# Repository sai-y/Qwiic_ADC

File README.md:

# Qwiic_ADC

Repo for an ADC chip that uses the Qwiic connector interface from Sparkfun

The ADC chip used here is the ADS7828EB

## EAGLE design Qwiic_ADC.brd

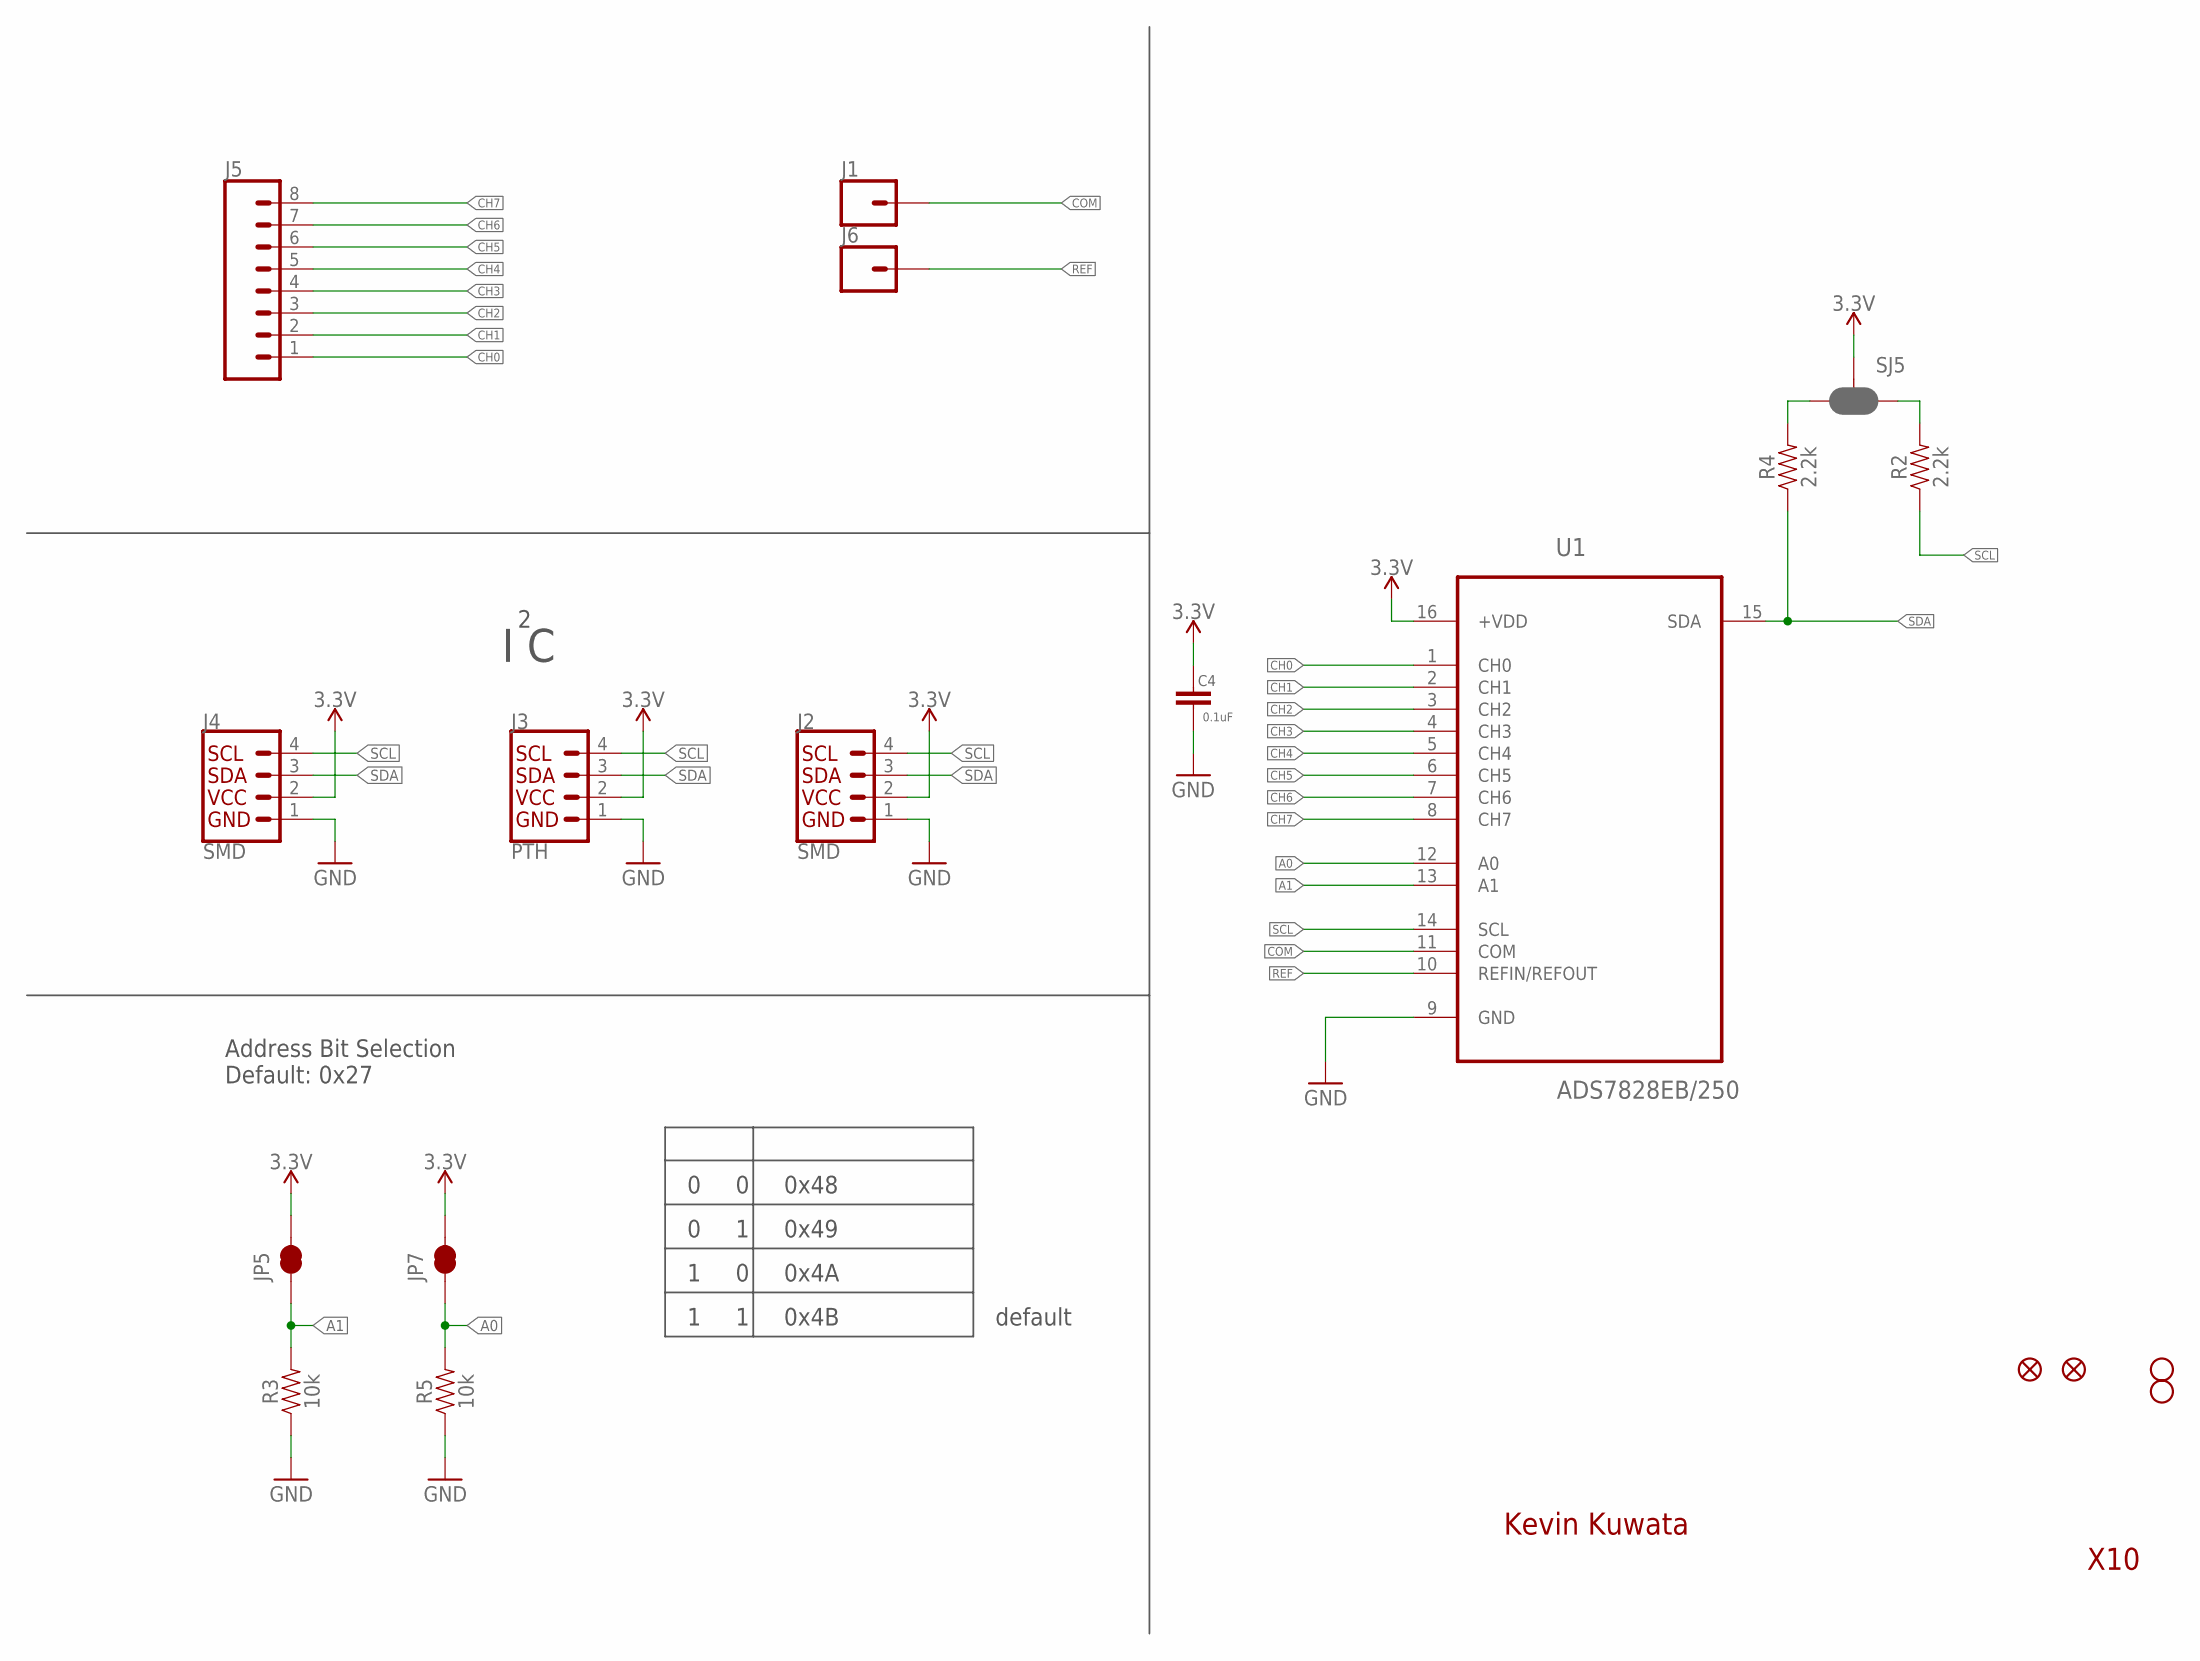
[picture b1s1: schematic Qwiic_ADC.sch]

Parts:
C4: 0.1uF; 0603
J1, J6: CONN_01PTH_NO_SILK_YES_STOP; 1X01_NO_SILK
J2, J4: SMD; 1X04_1MM_RA
J3: PTH; 1X04_NO_SILK
J5: CONN_08NO_SILK_FEMALE_PTH; 1X08_NO_SILK
JP2, JP6: FIDUCIALUFIDUCIAL; MICRO-FIDUCIAL
JP3, JP4: STAND-OFF
JP5, JP7: JUMPER-SMT_2_NC_TRACE_NO-SILK; SMT-JUMPER_2_NC_TRACE_NO-SILK
R2, R4: 2.2k; 0603
R3, R5: 10k; 0603
SJ5: SMT-JUMPER-_3-2-NC-PASTE_TALL; SMT-JUMPER_3-2-NC-PASTE_SILK_TALLER_A
U1: ADS7828EB/250; SOP65P640X120-16N

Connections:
3.3V: C4.1, J2.2 (VCC), J3.2 (VCC), J4.2 (VCC), JP5.2, JP7.2, SJ5.2, U1.16 (+VDD)
A0: JP7.1, R5.2, U1.12 (A0)
A1: JP5.1, R3.2, U1.13 (A1)
CH0: J5.1, U1.1 (CH0)
CH1: J5.2, U1.2 (CH1)
CH2: J5.3, U1.3 (CH2)
CH3: J5.4, U1.4 (CH3)
CH4: J5.5, U1.5 (CH4)
CH5: J5.6, U1.6 (CH5)
CH6: J5.7, U1.7 (CH6)
CH7: J5.8, U1.8 (CH7)
COM: J1.1, U1.11 (COM)
GND: C4.2, J2.1 (GND), J3.1 (GND), J4.1 (GND), R3.1, R5.1, U1.9 (GND)
REF: J6.1, U1.10 (REFIN/REFOUT)
SCL: J2.4 (SCL), J3.4 (SCL), J4.4 (SCL), R2.1, U1.14 (SCL)
SCL_PU1: R2.2, SJ5.1
SDA: J2.3 (SDA), J3.3 (SDA), J4.3 (SDA), R4.1, U1.15 (SDA)
SDA_PU1: R4.2, SJ5.3

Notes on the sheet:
Kevin Kuwata
X10
I C
Address Bit Selection Default: 0x27
0 0 0x48
0 1 0x49
1 0 0x4A
1 1 0x4B
default

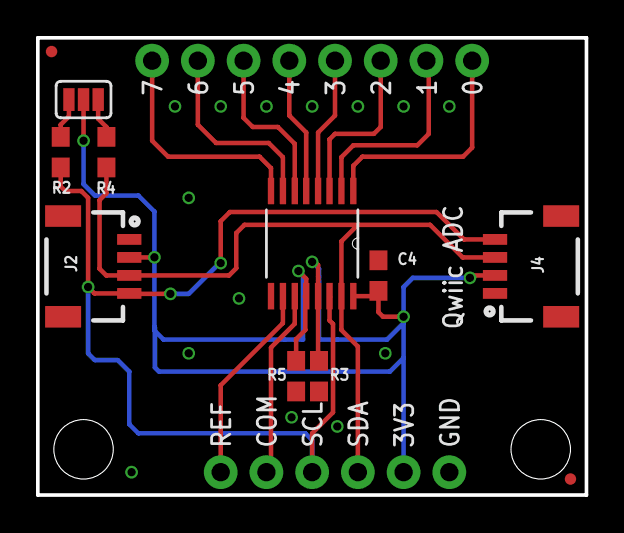
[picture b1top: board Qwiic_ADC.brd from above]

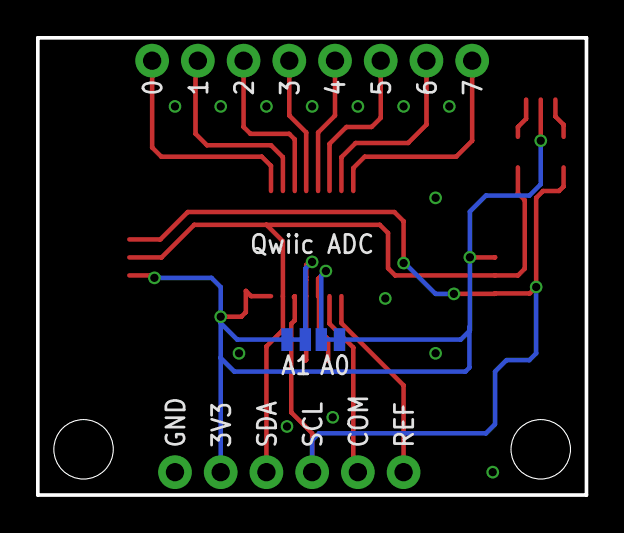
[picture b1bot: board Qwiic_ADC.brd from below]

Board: 2 copper layers, 30.5 x 25.4 mm, 19 parts (2 on the bottom side), 18 nets.

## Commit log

2018-05-22 Initializing repo
2018-06-03 Added frame to schematic
2018-06-03 adding image

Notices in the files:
parts and their libraries:
SparkFun-Resistors: Licensing: Creative Commons ShareAlike 4.0 International - https://creativecommons.org/licenses/by-sa/4.0
